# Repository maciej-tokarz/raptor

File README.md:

# Raptor

### Udostępniony kod wykorzystujesz na własną odpowiedzialność!

## Wstęp

Projekt jest moim pierwszym napisanym w Pythonie więc proszę o wyrozumiałość :-)

Raptor to aplikacja, dzięki której możliwe jest dozorowanie wybranego miejsca za pomocą czujki PIR, która identyfikuje naruszenie obszaru przez intruza. 
W takim przypadku wzbudzany jest alarm, który powiadamia ustalonych odbiorców o zdarzeniu sms-em oraz przez określony czas co sekundę rejestruje zdjęcia z kamery. 
Na zakończenie alarmu pierwszych sześć zdjęć jest wysyłanych e-mailem. Całość działa w oparciu o komputer Raspberry Pi. Do pisania kodu wykorzystuję [PyCharm](https://www.jetbrains.com/pycharm/).

Zainteresowanych zapraszam do współtworzenia Raptora.

[Dyskusja na grupie Malinowe Pi (Facebook) o projekcie](https://www.facebook.com/groups/malinowepi/permalink/433256330178355/) <<< Serdeczne dzięki za uwagi!

## Podstawowe funkcje programu

- Monitorowanie kilku zdefiniowanych obszarów,
- Raptor na starcie ustawia czas systemowy na podstawie wzorca wg. pool.ntp.org,
- dozoruje obszar czujką i śledzi jej wskazania,
- po otrzymaniu określonej ilości wskazań pozytywnych czujki aktywuje alarm,
- rozpoczęcie alarmu sygnalizowane jest sms-em o przykładowej treści “Raptor: alarm 2016-04-14 1123”, gdzie data i godzina to początek alarmu,
- alarm realizuje przede wszystkim swoją podstawową funkcję, to znaczy zapisuje serię 90 zdjęć w odstępach sekundowych,
- wykonanie zdjęcia determinuje wskazanie czujki – zdjęcie nie zostanie wykonane jeśli nie ma ruchu w chronionym obszarze,
- po zakończeniu serii, pierwszych sześć zdjęć zostanie wysłane e-mailem do określonych odbiorców,
- po wysłaniu e-maila Raptor będzie ponownie gotowy do działania i wskazania czujki mogą wywołać następny alarm,
- przed zapisem zdjęć program sprawdza ilość dostępnego miejsca na karcie i jeśli będzie go mniej niż 500MB to 10 najstarszych alarmów zostanie automatycznie usuniętych,
- codziennie o ustalonej godzinie Raptor wysyła kontrolne zdjęcie e-mailem,

Do przesyłania sms-ów wykorzystuję API dostępne np. tutaj: [mail2sms](https://www.smsapi.pl/mail2sms)

## Podzespoły

- Raspberry Pi,
- dedykowana kamera wraz podświetleniem IR,
- taśma łącząca kamerę, np. o długości dwóch metrów,
- czujka PIR,
- HUB USB niezbędny do zasilenia modemu GSM,
- modem GSM np. Huawei E3131h-2,
- UPS opisany poniżej,

## UPS

Dzięki pomocy Piotra "pimowo" z forum [nettemp.pl](http://nettemp.pl/forum/viewtopic.php?f=8&t=653&hilit=ups) będę również składał mini UPS do Raspberry. Piotr udostępnił [schemat](/docs/UPS_mini.png) do którego potrzebne są następujące podzespoły:

- 2 lub 3 ogniwa 18650 wraz z koszykiem
- zasilacz sieciowy 5V minimum 3A 
- ładowarka ogniw 18650 np. TP4056
- przetwornica DC/DC MT3608 step-up 5-28V 2A 
- dwie diody np. 1N5822

Piotr - serdeczne dzięki!

Jak powstawał UPS opisałem [tutaj](UPS.md).

## Do zrobienia

Projekt można, a nawet trzeba rozwijać. Do zrobienia jest choćby:

- zebranie ustawień w jednym miejscu (smtp, numery telefonów i adresy e-mail odbiorców)
- interfejs graficzny do zmiany powyższych ustawień oraz przeglądania zdjęć alarmów
- sterowanie programem komendami sms
- dodanie - po sms-ie informacyjnym o alarmie - połączenia z telefonem odbiorcy
- listę uzupełnię o informacje zebrane w [dyskusji na grupie Malinowe Pi na Facebook-u](https://www.facebook.com/groups/malinowepi/permalink/433256330178355/)

## Instalacja Raspbiana Jessie

Jako podstawę działania posłuży wersja:

[Minimal image based on Debian Jessie](https://www.raspberrypi.org/downloads/raspbian/)

Po zainstalowaniu należy:

- zmienić hasło administratora,
- rozszerzyć partycję na całą objętość karty,
- włączyć kamerę,
- włączyć obsługę GPIO
- włączyć obsługę Serial

## Instalacja karty WiFi

$ sudo nano /etc/wpa_supplicant/wpa_supplicant.conf

```
network={
    ssid="nazwa_sieci"
    psk="hasło"
}
```

## Instalacja Pythona

[INSTALLING PYTHON PACKAGES](https://www.raspberrypi.org/documentation/linux/software/python.md)

$ sudo apt-get update

$ sudo apt-get install python-picamera

$ sudo apt-get upgrade

## Instalacja modemu GSM

$ sudo apt-get install ppp usb-modeswitch wvdial

$ sudo reboot

## Instalacja Python Serial

$ sudo apt-get install python-serial

$ sudo apt-get update

$ sudo apt-get upgrade

## Instalacja klienta NTP

https://pypi.python.org/pypi/ntplib/

$ sudo cp /home/pi/ntplib-0.3.3/ntplib.py /usr/lib/python2.7/ntplib.py

## Instalacja Schedule

$ sudo apt-get install python-pip

$ sudo pip install schedule

## Aktualizacja Raspberry

$ sudo apt-get install rpi-update && sudo rpi-update && sudo reboot 

## Usuwanie pamięci tymczasowej instalatora na wypadek przerwania jego pracy

$ sudo rm /var/lib/dpkg/lock

$ sudo dpkg --configure -a

## Sprawdzenie wolnej przestrzeni systemu plików

$ df -Bm

## Usunięcie plików alarmu

$ sudo rm -rf /home/pi/alarms

## Uruchomienie skryptu Pythona

$ sudo python /home/pi/raptor.app/raptor.app.py

## Wyłączenie diody kamery

$ sudo nano /boot/config.txt

disable_camera_led=1

## Ustawienia modemu GSM

[Poradnik: Instalacja i obsługa modemu 3G](https://dug.net.pl/drukuj/132/huawei_e122___instalacja_i_obsluga_modemu_3g/)

$ sudo nano /etc/wvdial.conf

```
[Dialer Defaults]
Modem = /dev/ttyUSB0
Baud = 460800
SetVolume = 0
Dial Command = ATDT
FlowControl = NOFLOW
Init1 = ATZ

[Dialer modem-start]
Init1 = AT+CFUN=0
Init2 = ATZ+CFUN=1

[Dialer pin]
Init1 = AT+CPIN=1234

[Dialer orange]
Modem = /dev/ttyUSB0
Baud = 57600
Init1 = ATH
Init2 = ATE1
Init3 = AT+CGDCONT=1,"IP","internet"
Dial Command = ATD
Phone = *99#
Stupid mode = yes
Username = "internet"
Password = "internet"
Auto DNS = yes
```

## Uruchamianie wraz z systemem modemu i Raptora

$ sudo -i

$ nano /root/raptor.sh

```
#!/bin/bash

printf "\n"
printf "Uruchamiam modem...\n"
/usr/sbin/usb_modeswitch -v 12d1 -p 15ca -V 12d1 -P 1506 -M "55534243123456780000000000000011062000000100000000000000000000"
sleep 10
lsusb

printf "Nawiazanie polaczenia...\n"
wvdial modem-start >/dev/null 2>&1 || true
sleep 10

pon.wvdial pin orange
sleep 10

# printf "Uruchamiam Raptora!\n"
# cd /home/pi/raptor.app
# python app.py

# Print the IP address
_IP=$(hostname -I) || true
if [ "$_IP" ]; then
  printf "My IP address is:%s\n" "$_IP"
fi
```

$ chmod 755 raptor.sh

$ sudo nano /etc/rc.local

```
/root/raptor.sh &
exit 0
```
sudo bash raptor.sh

___
Maciej Tokarz © My-Poi!

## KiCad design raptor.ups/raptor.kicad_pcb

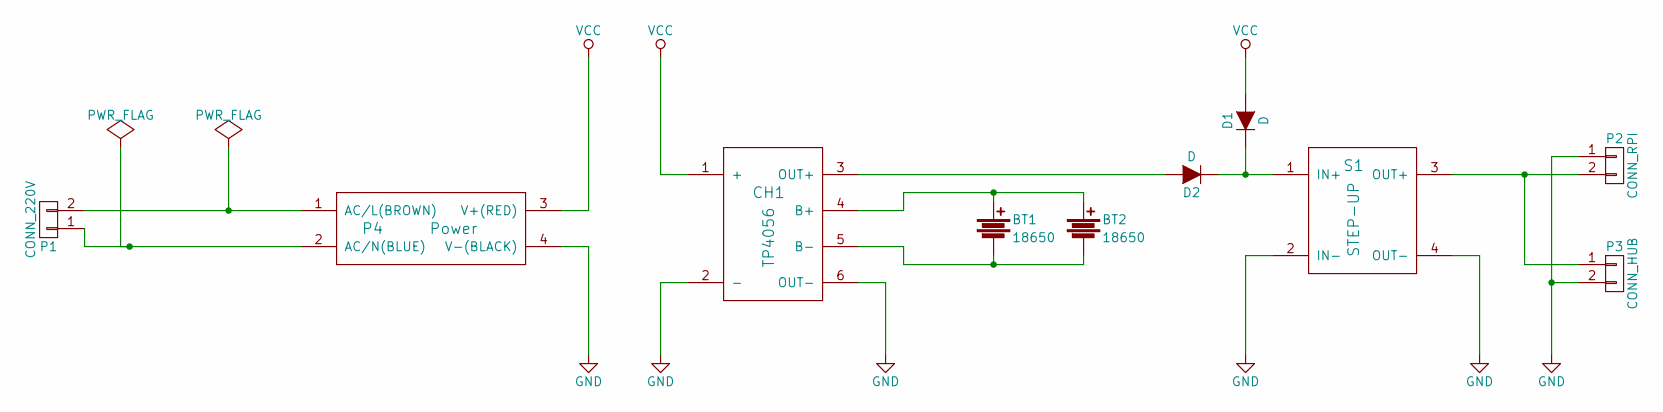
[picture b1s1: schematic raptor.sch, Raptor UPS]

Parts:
BT1, BT2: 18650
CH1: TP4056
D1, D2: D; Diode_DO-201AD_Horizontal_RM15
P1: CONN_220V; TerminalBlock_2pin_5mm
P2: CONN_RPI; TerminalBlock_2pin_5mm
P3: CONN_HUB; TerminalBlock_2pin_5mm
P4: Power; GPV-20-5
S1: STEP-UP

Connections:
GND: CH1.2 (-), CH1.6 (OUT-), P2.1, P3.2, P4.4 (V-(BLACK)), S1.2 (IN-), S1.4 (OUT-)
unnamed: BT1.1, BT2.1, CH1.4 (B+)
unnamed: BT1.2, BT2.2, CH1.5 (B-)
unnamed: CH1.3 (OUT+), D2.2 (A)
unnamed: D1.1 (K), D2.1 (K), S1.1 (IN+)
unnamed: P1.1, P4.2 (AC/N(BLUE))
unnamed: P1.2, P4.1 (AC/L(BROWN))
unnamed: P2.2, P3.1, S1.3 (OUT+)
VCC: CH1.1 (+), D1.2 (A), P4.3 (V+(RED))

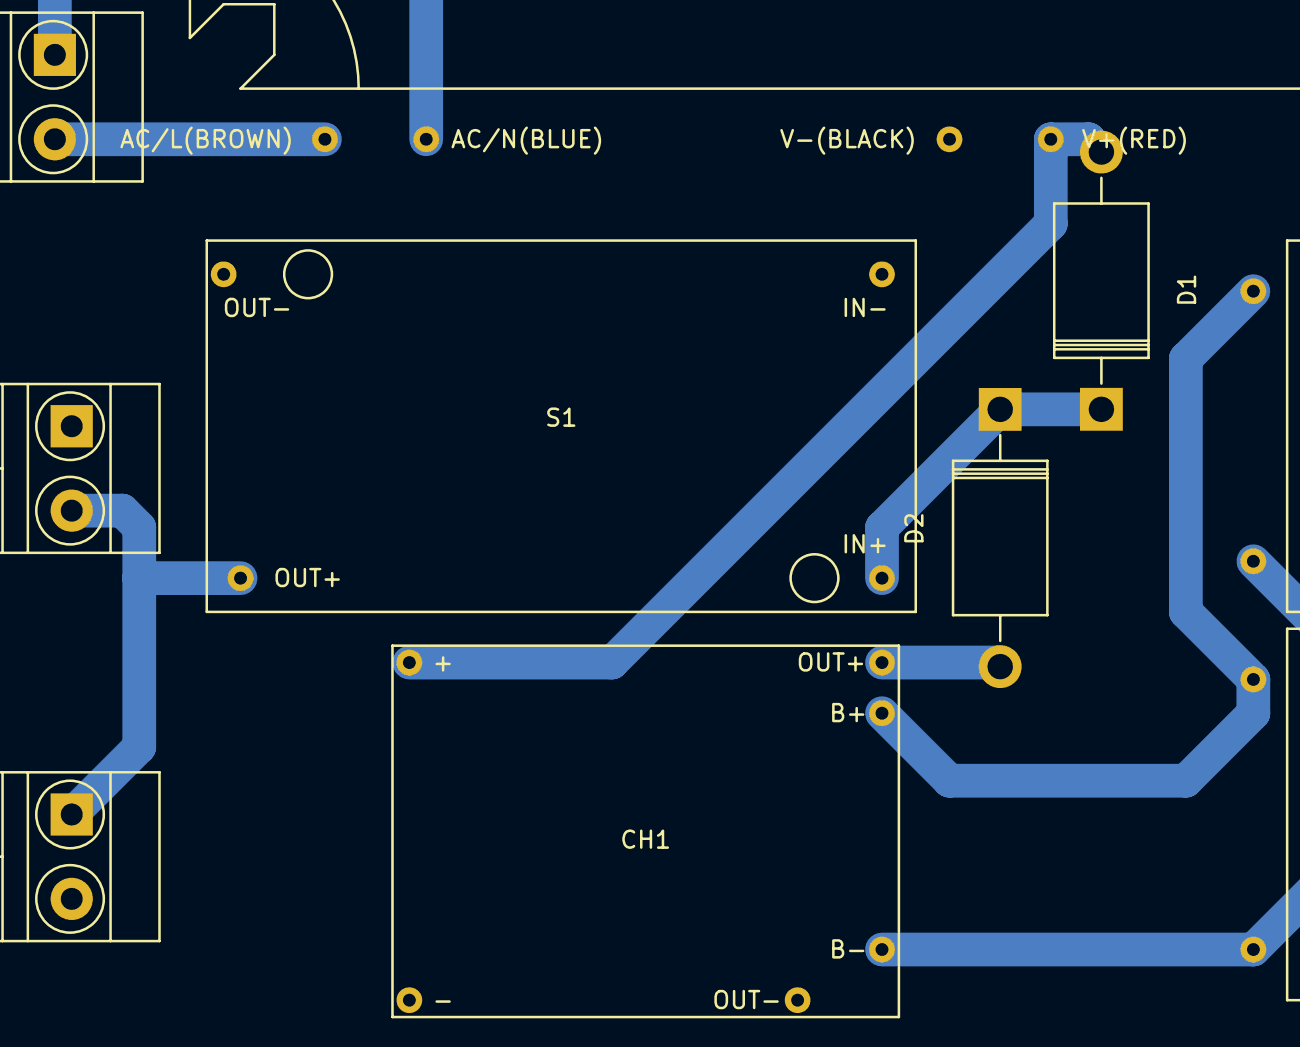
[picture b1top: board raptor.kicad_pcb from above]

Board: 2 copper layers, 10 parts (0 on the bottom side), 9 nets.

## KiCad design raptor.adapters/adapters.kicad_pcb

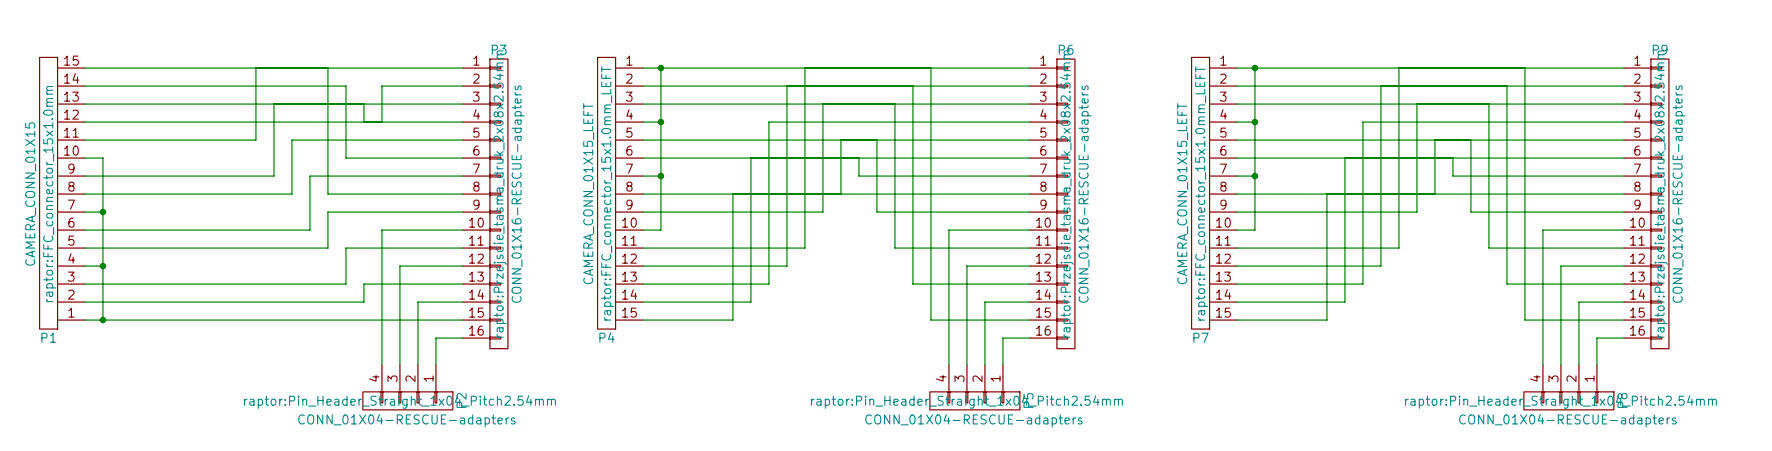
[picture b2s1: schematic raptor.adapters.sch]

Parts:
P1: CAMERA_CONN_01X15; FFC_connector_15x1.0mm
P2, P5, P8: CONN_01X04-RESCUE-adapters; Pin_Header_Straight_1x04_Pitch2.54mm
P3, P6, P9: CONN_01X16-RESCUE-adapters; Przejscie_tasma_druk_2x08x2.54mm
P4, P7: CAMERA_CONN_01X15_LEFT; FFC_connector_15x1.0mm_LEFT

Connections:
unnamed: P1.1, P1.4, P1.7, P1.10, P3.15
unnamed: P1.2, P3.13
unnamed: P1.3, P3.11
unnamed: P1.5, P3.9
unnamed: P1.6, P3.7
unnamed: P1.8, P3.5
unnamed: P1.9, P3.3
unnamed: P1.11, P3.1
unnamed: P1.12, P3.2
unnamed: P1.13, P3.4
unnamed: P1.14, P3.6
unnamed: P1.15, P3.8
unnamed: P2.1, P3.16
unnamed: P2.2, P3.14
unnamed: P2.3, P3.12
unnamed: P2.4, P3.10
unnamed: P4.1, P4.4, P4.7, P4.10, P6.15
unnamed: P4.2, P6.13
unnamed: P4.3, P6.11
unnamed: P4.5, P6.9
unnamed: P4.6, P6.7
unnamed: P4.8, P6.5
unnamed: P4.9, P6.3
unnamed: P4.11, P6.1
unnamed: P4.12, P6.2
unnamed: P4.13, P6.4
unnamed: P4.14, P6.6
unnamed: P4.15, P6.8
unnamed: P5.1, P6.16
unnamed: P5.2, P6.14
unnamed: P5.3, P6.12
unnamed: P5.4, P6.10
unnamed: P7.1, P7.4, P7.7, P7.10, P9.15
unnamed: P7.2, P9.13
unnamed: P7.3, P9.11
unnamed: P7.5, P9.9
unnamed: P7.6, P9.7
unnamed: P7.8, P9.5
unnamed: P7.9, P9.3
unnamed: P7.11, P9.1
unnamed: P7.12, P9.2
unnamed: P7.13, P9.4
unnamed: P7.14, P9.6
unnamed: P7.15, P9.8
unnamed: P8.1, P9.16
unnamed: P8.2, P9.14
unnamed: P8.3, P9.12
unnamed: P8.4, P9.10

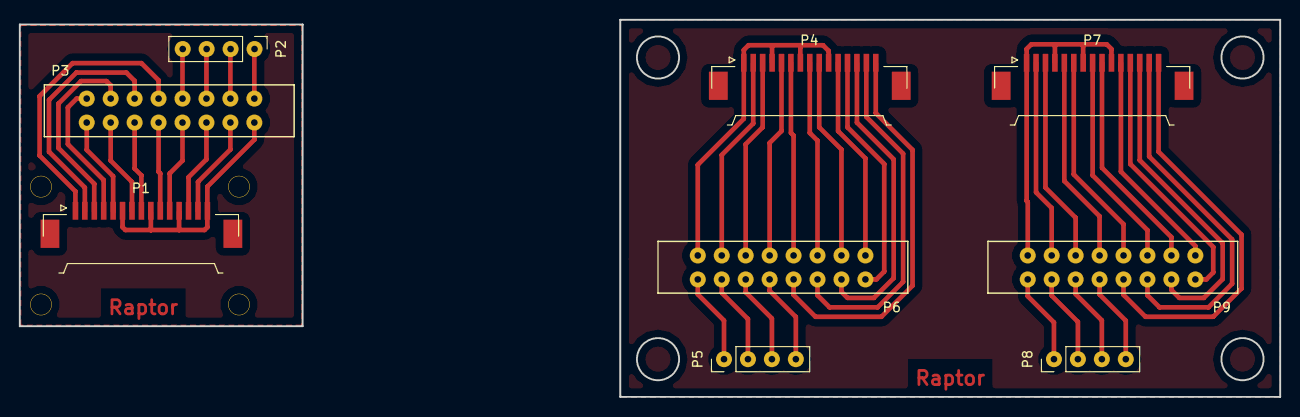
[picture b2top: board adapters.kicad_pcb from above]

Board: 2 copper layers, 133.7 x 40.0 mm, 9 parts (0 on the bottom side), 48 nets.

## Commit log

2016-04-20 Wersja 1.0
2016-04-20 Dopasowanie ikony.
2016-04-20 Rozmiar ikony cd.
2016-04-20 Uzupełniłem Readme.
2016-04-20 Zlokalizowałem czas zdjęcia wg, harmonogramu.
2016-04-20 Dodałem info o UPS.
2016-04-20 dodałem TODO.
2016-04-20 Korekta TODO.
2016-04-21 Poprawka opisu Readme.
2016-04-21 Readme cd.
2016-05-15 Nauka KiCada
2016-05-15 Nauka KiCada cd.
2016-05-16 Postępy nad schematem...
2016-05-16 Pierwsze ścieżki :)
2016-05-18 Płytka prawie gotowa!
2016-05-18 Jeszcze poprawki płytki PCB UPS-a.
2016-05-19 Praktycznie gotowa PCB UPS-a.
2016-05-19 Dodałem pdf z wydrukiem pcb.
2016-05-19 Drobna korekta pcb.
2016-05-19 Odwrócenie wydruku.
2016-05-22 Drobna korekta int to str.
2016-05-25 Poprawka wysyłania e-maila.
2016-05-26 Korekta wysyłania e-maila.
2016-05-26 Korekta SMTP cd.
2016-05-26 Drobne korekty opisu i email_message.py
2016-05-26 Jeszcze drobne poprawki kodu wysyłania e-maila.
2016-05-26 Zmiana serwera smtp na gmaila.
2016-05-27 Przeniesienie uruchomienia modemu GSM do autostartu systemu.
2016-05-27 Dodanie komentarza.
2016-05-28 Dodałem opis budowy UPS-a.
2016-05-28 Mieszanie z nazwą folderu.
2016-05-28 Cd. mieszania
2016-05-28 Podpis.
2016-05-28 Podpis cd.
2016-05-28 Poprawa linku.
2016-05-28 Jeszcze korekta odnośników.
2016-05-28 Korekta opisu UPS-a.
2016-05-28 Opis.
2016-05-29 Korekta opisu.
2016-05-29 KKorekta opisu cd.
2016-05-29 Opis UPS-a cd.
2016-05-29 Uzupełnienie opisu UPS-a.
2016-05-29 Opis Ups-a.
2016-05-29 Opis UPS.
2016-05-29 Opis README.
2016-06-02 Odnośnik do dyskusji na FB.
2016-06-07 Dodałem plik ustawień oraz loggera. Jeszcze nie testowana całość - w trakcie przeróbek.
2016-06-07 Poprawka README
2016-06-19 Reboot nie wchodzi w grę bowiem modem nie uruchamia się ponownie. Nanoszenie niezbednych poprawek.
2016-06-19 Dodanie do configu godziny codziennego zdjęcia kontrolnego.
2016-06-19 Jeszcze poprawki i niebawem testowanie całości.
2016-06-20 Alarm działa i rozpoczynają się tygodniowe testy. Możliwe korekty.
2016-06-25 Poprawiłem moduł wysyłania e-maila. Jak na razie wszystko OK!
2016-06-25 Jeszcze drobna korekta kodu e-maila.
2016-06-29 W sumie nic, test usuwania starych alarmów OK!
2017-03-11 Dodaję adapter taśma FFC > kable do kamery.
2017-03-11 Kamera cd.
2017-03-11 Dodałem pdfa
2017-03-12 Korekta płytki adaptera kamery
2017-03-12 Korekta podglądu projektu adaptera
2017-03-12 Przesunąłem złącze FFC od otworów.
2017-03-12 pcb.pdf
2017-03-15 Test
2017-03-15 Działa
2017-03-17 Pierwsze poprawki klasy Pir
2017-03-17 Porządki z kodem cd. - config
2017-03-17 Poprawka kodu kamery
2017-03-17 Drobne poprawki kodu.
2017-03-19 Początki obiektowości
2017-03-19 Początki obiektowości cd.
2017-03-31 Prace nad płytką
2017-03-31 Usunąłem niepotrzebne pliki.
2017-03-31 Korekta komend
2017-03-31 Korekta wymiaru płytki
2017-03-31 Gotowy negatyw pcb adaptera.
2017-03-31 Aktualizacja pcb.pdf
2017-03-31 Poprawka negatywu
2017-04-02 Korekta negatywu.
2017-04-03 Dodałem pdf CMYK - http://www.pdf2cmyk.com/
2017-04-08 Zapis postepów - kamery
2017-04-08 Działają kamery i czujki...
2017-04-08 Składam całość
2017-04-09 Poprawiona architektura programu.
2017-04-09 Korekta wykonywania zdjęć.
2017-04-09 Drobne poprawki.
2017-04-09 Drobne poprawki cd.
2017-04-09 Prawie gotowe, jeszcze testy...
2017-04-10 Dodałem obsługę błędów przy wykonywaniu zdjęcia.
2017-04-13 Dodaję adapter na przejścia do taśmy.
2017-04-13 Opracowałem płytkę na złącze pcb taśmy.
2017-04-13 Jeszcze poprawka płytki.
2017-04-14 Korekty pozytywów pcb.
2017-04-14 Prace nad płytką cd.
2017-04-14 Korekta pcb adaptera kamery.
2017-04-15 Korekta średnic pinów.
2017-04-15 Korekty pcb kamery.
2017-04-18 Koniec wersji publicznej.
2017-06-05 Korekta adaptera kamery.
2017-07-11 drobne korekty kodu
2017-07-12 drobne korekty
2017-07-12 jeszcze parę poprawek
